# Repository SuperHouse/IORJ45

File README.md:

I/O Breakout To RJ45
====================
Copyright 2017 SuperHouse Pty Ltd  
SuperHouse site:  <www.superhouse.tv>  

Breaks out a pair of 2x6 pin headers to 4 x RJ45 sockets.

Features:

 * 2 x 2x6 pin headers
 * 4 x RJ45 sockets
 * Each RJ45 socket provides 4 x data lines, GND, VIN, IOREF, and RESET
 * 1k resistor in series with each data line

More information is available at:

  http://www.superhouse.tv/iorj45

INSTALLATION
------------
The design is saved as an EAGLE project. EAGLE PCB design software is
available from www.cadsoftusa.com free for non-commercial use. To use
this project download it and place the directory containing these files
into the "eagle" directory on your computer. Then open EAGLE and
navigate to the project.

DISTRIBUTION
------------
The specific terms of distribution of this project are governed by the
license referenced below.

LICENSE
-------
Licensed under the TAPR Open Hardware License (www.tapr.org/OHL).
The "license" folder within this repository also contains a copy of
this license in plain text format.

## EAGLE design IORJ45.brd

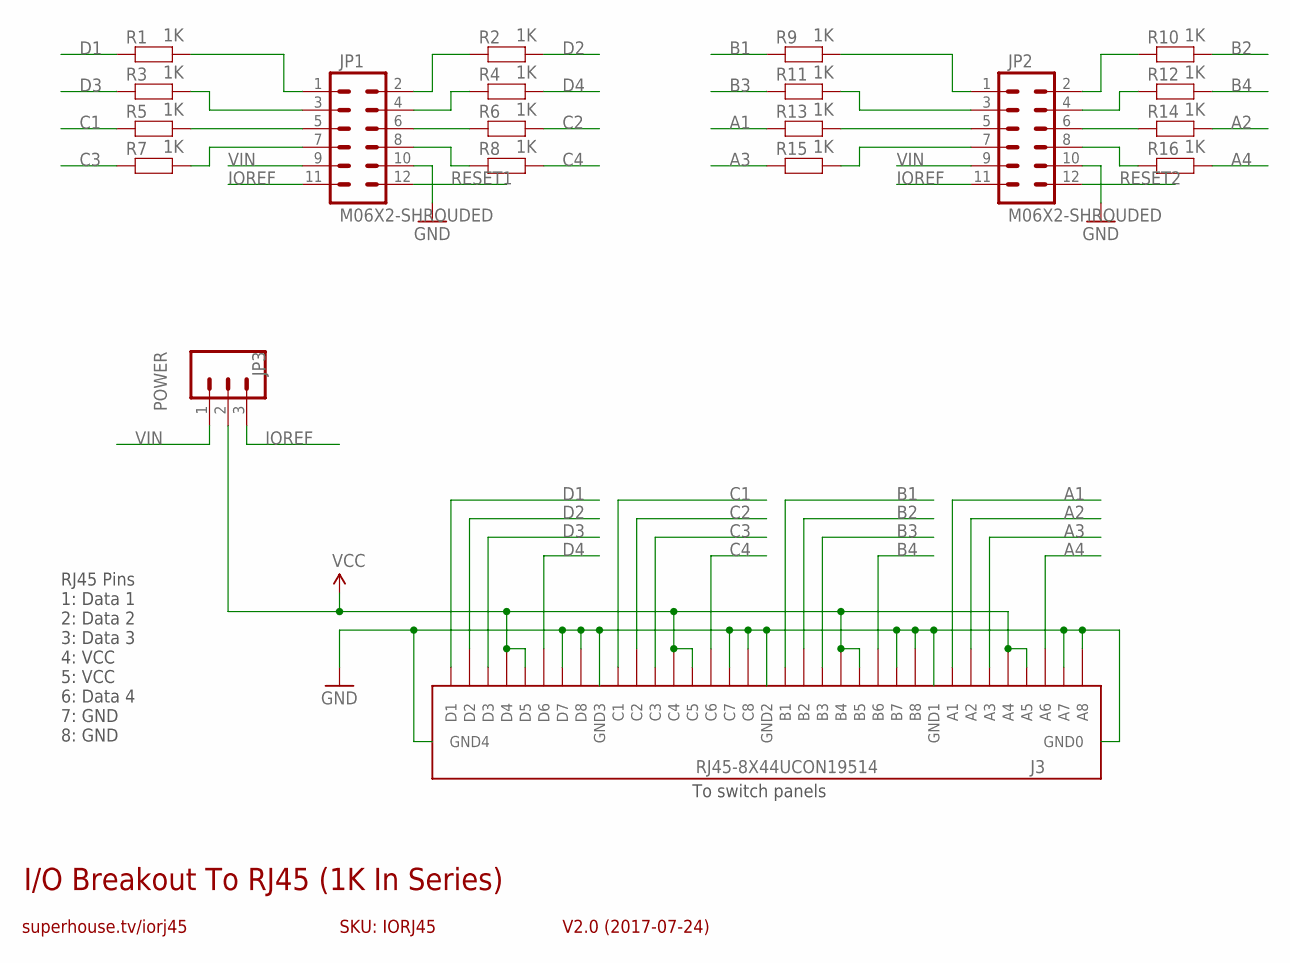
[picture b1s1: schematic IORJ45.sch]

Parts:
J3: RJ45-8X44UCON19514; RJ45-8X4
JP1, JP2: M06X2-SHROUDED; 2X6-SHROUDED
JP3: POWER; 1X03-P
R1, R2, R3, R4, R5, R6, R7, R8, R9, R10, R11, R12, R13, R14, R15, R16: 1K; R0603

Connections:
A1: J3.A1, R13.1
A2: J3.A2, R14.2
A3: J3.A3, R15.1
A4: J3.A6, R16.2
B1: J3.B1, R9.1
B2: J3.B2, R10.2
B3: J3.B3, R11.1
B4: J3.B6, R12.2
C1: J3.C1, R5.1
C2: J3.C2, R6.2
C3: J3.C3, R7.1
C4: J3.C6, R8.2
D1: J3.D1, R1.1
D2: J3.D2, R2.2
D3: J3.D3, R3.1
D4: J3.D6, R4.2
GND: J3.A7, J3.A8, J3.B7, J3.B8, J3.C7, J3.C8, J3.D7, J3.D8, J3.GND0, J3.GND1, J3.GND2, J3.GND3, J3.GND4, JP1.10, JP2.10
IOREF: JP1.11, JP2.11, JP3.3
unnamed: JP2.5, R13.2
unnamed: JP1.5, R5.2
unnamed: JP1.3, R3.2
unnamed: JP1.1, R1.2
unnamed: JP1.7, R7.2
unnamed: JP2.3, R11.2
unnamed: JP2.1, R9.2
unnamed: JP1.8, R8.1
unnamed: JP1.6, R6.1
unnamed: JP1.4, R4.1
unnamed: JP1.2, R2.1
unnamed: JP2.7, R15.2
unnamed: JP2.6, R14.1
unnamed: JP2.8, R16.1
unnamed: JP2.4, R12.1
unnamed: JP2.2, R10.1
RESET1: JP1.12
RESET2: JP2.12
VCC: J3.A4, J3.A5, J3.B4, J3.B5, J3.C4, J3.C5, J3.D4, J3.D5, JP3.2
VIN: JP1.9, JP2.9, JP3.1

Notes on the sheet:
I/O Breakout To RJ45 (1K In Series)
V2.0 (2017-07-24)
superhouse.tv/iorj45
SKU: IORJ45
To switch panels
RJ45 Pins 1: Data 1 2: Data 2 3: Data 3 4: VCC 5: VCC 6: Data 4 7: GND 8: GND

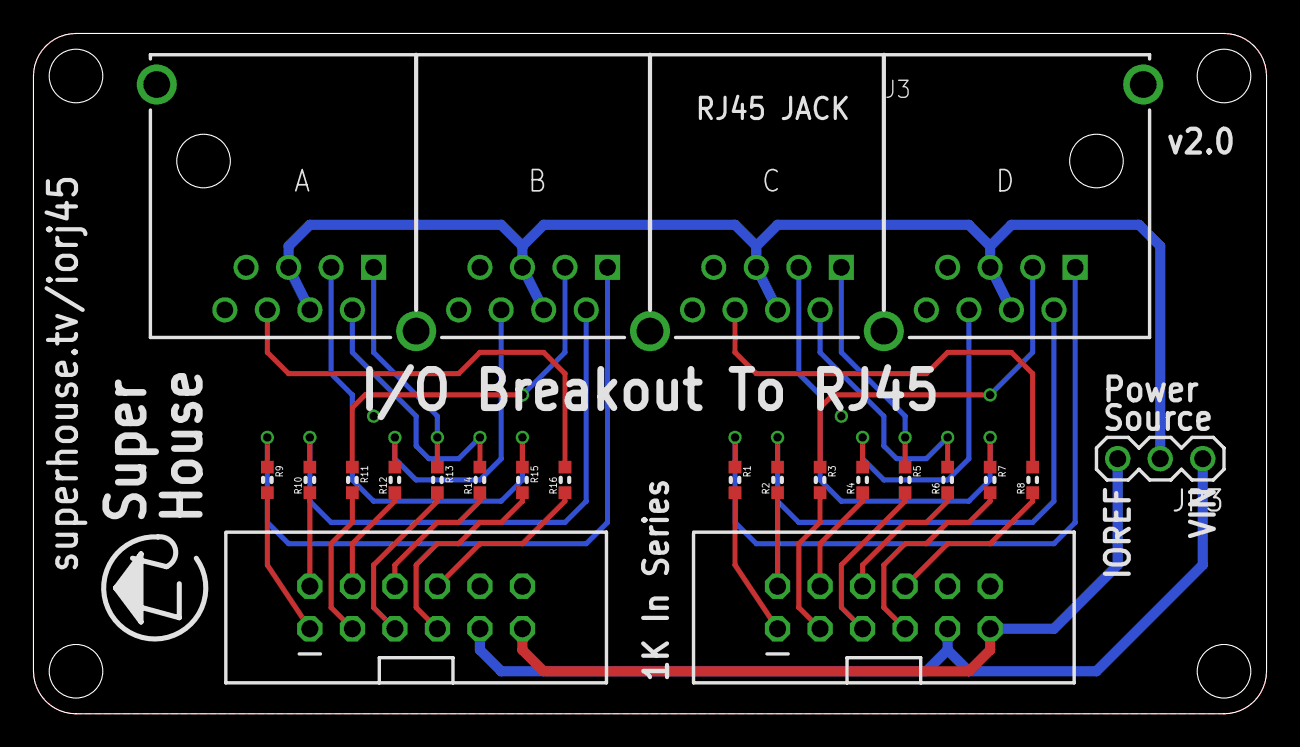
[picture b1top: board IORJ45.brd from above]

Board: 2 copper layers, 73.7 x 40.6 mm, 20 parts (0 on the bottom side), 36 nets.

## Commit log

2017-07-20 Initial project import with files from IOBRIN
2017-07-25 Converted to 2x6 header for v2.0 release
2019-09-13 Part replacement using SuperHouse libraries

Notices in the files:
IORJ45.brd:
(C)2017 SuperHouse Automation Pty Ltd
parts and their libraries:
freetronics-original: Licensing: CC v3.0 Share-Alike You are welcome to use this library for commercial purposes.
